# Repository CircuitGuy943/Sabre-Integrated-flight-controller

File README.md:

I am currently trying to build my own drone from scratch, and slowly replace every component with my own, from creating fully custom PCBs for the flight controller or ESCs, to making a 3D printed drone chassis etc etc. And this is the fully fledged, multi functional, cool-looking flight controller. I present to you:

# *SABRE!*

For one of my biggest projects yet I designed a jack of all trades custom flight controller board. It also comes with custom firmware, or if possible compatibility with betaflight or other FC firmware out there. At it's core are two PCBs arranged in a stackup with the "top" and "bottom" sections. The two PCBs connect through the common 2.54mm pitch headers and stack on top of eachother and each serve to provide enough space for all the components and separate the sensitive digital components from the electromagnetic potential of the motor power rails. The bottom board houses E-Fuse protection and an INA226 current monitor to protect the boards, including powered FPV feed with the AT7456E and TX5813, accompanied by four MOSFET powered 12V LED strip channels. The top booard houses a powerful STM32F765VGT CPU which will, *fingers crossed,* be more than enough to run automatic flight levelling software quickly enough to not crash. Followed by a micro SD card slot for storing flight telemetry, programmable DIP switched for easy settings, BNO08x 9-DOF sensor module, segment display and pushbuttons for easy configuration without needing to reupload code and a BMP580 barometic sensor. More than I (or you) will ever need to fly a 4 blade, 1KG piece of PETG plastic :)

### Bottom Board:

Half of the bottom PCB houses the power delivery circuitry. This includes a dedicated TPS259850 chip, or an E-Fuse, required protection option for a drone that operates at around 20A sustained and 40A current peaks. Thanks to it's extremely low RDS on, basically no power is wasted, and it trips the circuit in a matter of microseconds when too much current is detected, which makes it extremely useful for a drone full of sensitive circuitry, compared to a traditional wire fuse. Followed by that is an INA226 chip, this aims to precisely monitor the current consumption of the entire drone, helping to predict flight times and efficiently manage battery health, through the use of a shunt resistor sized to the expected current draw. The current planes are optimized to make proper use of the different outer and inner layer thicknesses and properly distribute current with minimal heat up.

The other part of the bottom PCB houses the RF circuitry for the FPV system LED drivers togethor with power regulators that power the 12V rail for the LED drivers and the 5V rail for the FPV system and other 5V chips. The 12V power regulator (TPS55289) and the 5V regulator (TPS63070) both use the safest and most reliable layouts possible and are positioned to spatially divide the high ~32A currents on the bottom power distribution circuitry from the rest of the bottom board, a slide switch also controls the power supply to the TX5813 module, as this consumes the most out of the other board circuitry, at about ~200mA, this should help to increase flight time by cutting wasted power when the FPV function isn't being used. CSD16340 MOSFETS also serve to drive 4 seperate 12V LED strip channels, these I plan to connect to LED strips and create cool illuminations off of my drone.

The RF circuitry benefits from an impedance accurate JLC-3313 stackup and use of coplanar waveguide routing with via fencing, tearsrops and udnerpad via router to insure the least impedance mismatch possible. The actual RF system is composed of an external camera connector, or simple pin header (capable of reading almost any FPV camera such as the Caddx Ant Lite). The video signal is then passed through a meticulously routed 75ohm impedance matched trace into a MAX7456EUI (Or a newer drop in AT7456E replacement, pin to pin compatible), this module serves to inject an OSD (On screen display) into the video feed through communication with the STM32 MCU for easy sending of telemtry data like battery voltage, speed, altitude etc. The output from the OSD injection chip is then routed through another impedance matched trace with SAG correction into the video input of the TX5813. This modules handles the complicated circuitry of converting the video feed (~6MHz) into a radio signal of ~5.8GHz. That RF is then routed even more carefuly for the short length (~8mm) of the SMA launch into the SMA connector then into any respective 5.8GHz FPV antenna. (I also have a complemintary project for a 5.8GHz FPV reciever in another repository)

### Top Board:

Flying the drone is an STM32F765VGT CPU with up to 216MHz clock speed, hopefully resulting in almost perfect drone levelling and flight, on the other side of the board is also a USB C receptacle for programming the STM CPU, and powering the board while doing so (everything except the motors, of course, I also included diodes to prevent power backfeed). Close by is a BNO08x 9-DOF accelerometer, gyroscope and magnetometer, complete with an integrated 32-bit ARM Cortex-M0+ for quick sensor fusion with pre built firmware (meaning I have to code waaaay less :D). Motor PWM outputs for the ESCs also connected directly to PWM channels on the STM32 and two solder bridgeable connections to allow me to use the 5V supply from the ESCs in case my 5V regulator doesn't function properly under load (I've had bad experience with voltage regulators). Several voltage indicator LEDs are also placed near the USB C port at the back. Then there is also an UART FPC port designed to connect to a separate GPS board (large board for good GPS recieving power, check my other repositories) on the left side of the board. A 7 segment, 4 digit bitbanged display and several tactile pushbottoms also occupy the centre of the board, quite useless but they might be useful in changing more accute settings without having to reupload firmware every time. A micro SD card also connects through 4 channel SPI to STM32, I plan to use this to store settings or flight telemetry information that I could analyze while debugging. Powering all that is a 3.3V regulator (LMR51430XF), simplest (and therefore most reliable) I could find. And several other breakout headers for power/functionality. PWM inputs from the radio remote is recieved through a 3x8 header pinout designed for my specific radio reciever module.

## Features:
- Fully integrated design:
	- Custom firmware uploadable
	- Power distribution and control in one place
	- Dual stacked PCB design
 	- No screw, no wire inter board connection

- Power
	- Extremely low RDS protection e-Fuse (us trip time)
 	- INA226 current and voltage monitoring
  	- Backup/calibration voltage divider monitoring
  	- Fully optimized current planes, 40A+ capability
  	- Firmware built in battery management and flight warning system
  	- Meticulously designed 5V, 12V and 3.3V switching voltage regulators
  	- Backup ESC 5V supply availible
  	- LED indicators for power rail status
  	- 4 channel driver for 12V LED strips
  	- Power switch for TX5813 module for longer flight times

- Fully integrated FPV support
	- MAX7456/AT7456E OSD injection into FPV feed
	- Channel switch ability
	- TX5813 RF launch module
	- Accurate and reliable RF design
 	- Designed for impedance matched JLC 3313 stackup
 
- Flight Control
	- USB C programming connection 
	- Powerful STM32F765VGT CPU
 	- MicroSD card slot (For inflight telemtry storage)
  	- Programmable DIP switches
  	- Display/pushbuttons for setting adjustment without code reupload
  	- BNO08x 9-DOF sensor module with built in sensor fusion
  	- BMP580 Barometric sensor
  	- UART FPC connection for external GPS board
  	- Extra power and I2C debug headers
  	- 7 input PWM channels
  	- 4 ESC output PWM channels

## PCB
This is the PCB, with L1 to L4 Layers, silkscreen for both layers and an all layers view

And here is the schematic

## Firmware Overview
I've included some basic firmware (**untested**) that should get the TFT display working out of the box with a quick upload from arduino IDE

## BOM:
The BOM list for the actual PCB components is in the BOM folder section and here is also a BOM list for all the other components I plan to buy for this:

- PCB             $378.08		
- Antenna         $7.77      https://www.aliexpress.com/item/1005006153683653.html		
- 90 degree SMA   $4.51      https://www.aliexpress.com/item/1005005665998117.html						
- TX5813 module   $15.82     https://www.aliexpress.com/item/1005011698073364.html
											
Total			      $406.18

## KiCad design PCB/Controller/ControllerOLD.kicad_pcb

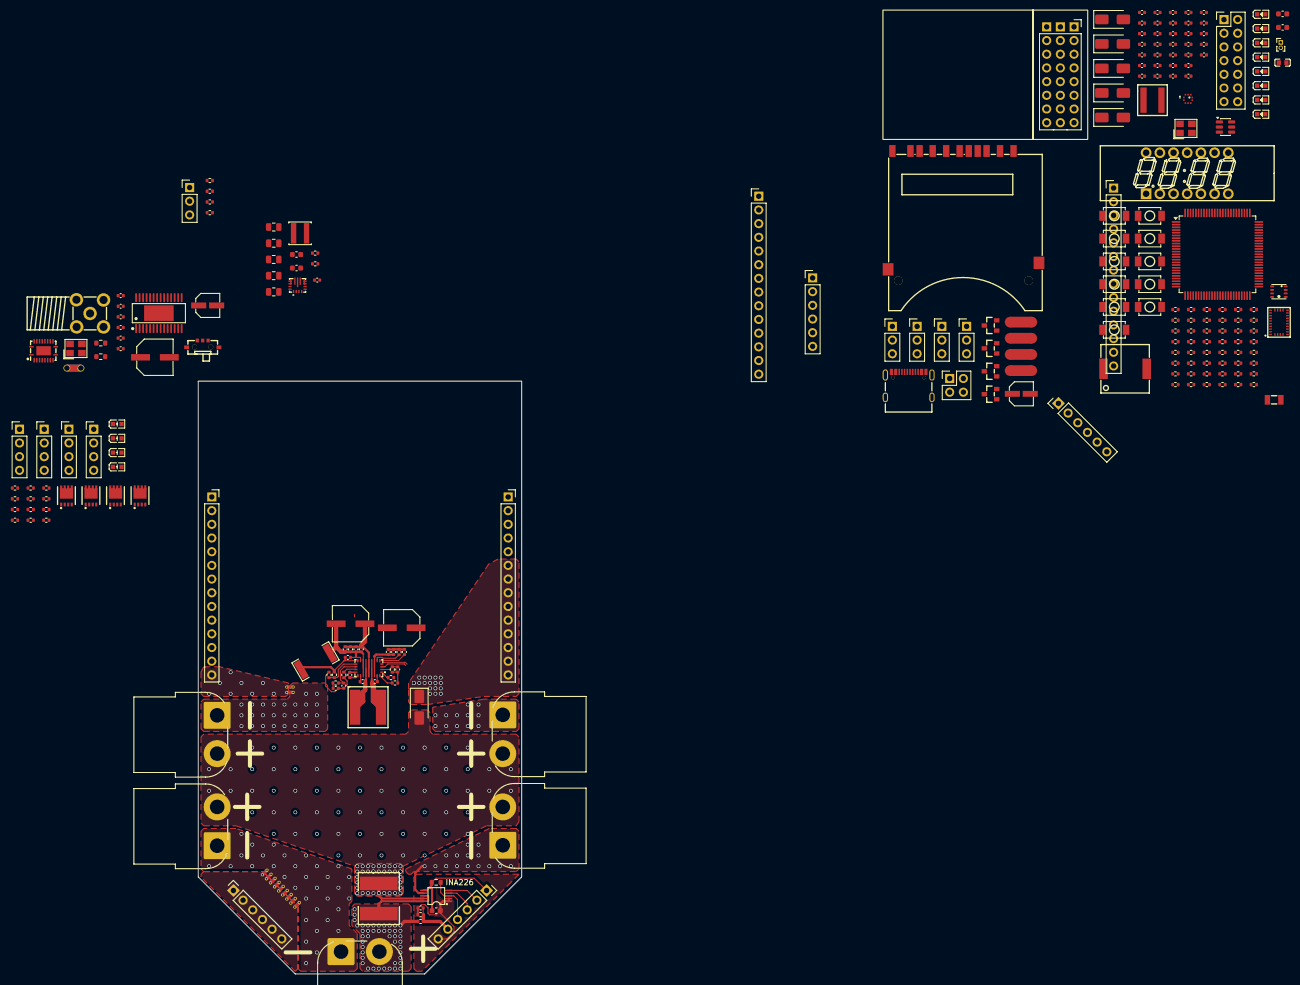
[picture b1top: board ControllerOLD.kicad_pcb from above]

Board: 4 copper layers, 60.0 x 110.0 mm, 254 parts (1 on the bottom side), 202 nets.

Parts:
BUZ1: CPT-9019S-SMT-TR; BUZ-SMD_L9.0-W9.0-P8.00-LS9.3
C1: 0.1uF; C_0603_1608Metric
C2, C11, C14, C15, C26, C27, C29, C30, C31, C32, C33, C34, C36, C37, C38, C41, C44, C45, C46, C47, C48, C49, C50, C51, C63, C64, C67: 100nF; C_0402_1005Metric
C3, C6: 10uF; C_0603_1608Metric
C4, C5: 10uF; C_0805_2012Metric
C7, C8, C9: 22uF; C_0805_2012Metric
C10, C57, C58: 2.2uF; C_0402_1005Metric
C12, C13: 22uF; C_0603_1608Metric
C16, C19, C20, C21, C22: 22uF; C_0402_1005Metric
C17: 4.7uF; C_0402_1005Metric
C18, C28: 22nF; C_0402_1005Metric
C23: 3300pF; C_0402_1005Metric
C24: 330pF; C_0402_1005Metric
C25: 47uF; CAP-SMD_BD6.3-L6.6-W6.6-LS7.2-FD
C35, C43, C56, C68: 10uF; C_0402_1005Metric
C39, C40, C60, C61: 20pF; C_0402_1005Metric
C42, C66: RVT1C220M0405_C3356_22uF; CAP-SMD_BD4.0-L4.3-W4.3-FD-LS5.3
C52, C53, C54, C55, C65: 1uF; C_0402_1005Metric
C59, C62: 6.8pF; C_0402_1005Metric
CN1: XT60PW_M; AMASS_XT60PW-M_1x02_P7.20mm_Horizontal
CN2, CN4, CN5, CN6: XT60PW_F; AMASS_XT60PW-F_1x02_P7.20mm_Horizontal
Card1: SD-006M; SD-SMD_SD-006M
D1, D2, D3, D4, D5, D6: SS34; D_SMA
J1, J2, J3, J4: Conn_01x04_Pin; PinHeader_1x04_P2.54mm_Vertical
J5, J6, J7, J8, J10: Conn_01x03_Pin; PinHeader_1x03_P2.54mm_Vertical
J9: Conn_01x02_Pin; PinHeader_1x02_P1.00mm_Vertical
J11: Conn_02x07_Top_Bottom; PinHeader_2x07_P2.54mm_Vertical
J12: Conn_02x02_Top_Bottom; PinHeader_2x02_P2.54mm_Vertical
J13, J18: Conn_01x14_Pin; PinHeader_1x14_P2.54mm_Vertical
J14, J19: Conn_01x06_Pin; PinHeader_1x06_P2.54mm_Vertical
J15, J20: Conn_01x14_Socket; PinSocket_1x14_P2.54mm_Vertical
J16, J17: Conn_01x06_Socket; PinSocket_1x06_P2.54mm_Vertical
L1: XFL4020-152MEC; IND-SMD_L4.0-W4.0-A
L2: FCM1608KF-601T03; L0603
LED1: FJ2481CH; LED-SEG-TH_14P-L32.2-W10.2-P2.54-S7.62-BL
LED2, LED11, LED12, LED13, LED14, LED15, LED16: KT-0603YG; LED0603-RD
LED3: KT-0603R; LED0603-RD
LED4, LED5, LED6, LED7: KT-0603W; LED0603-R-RD_WHITE
NT1, NT7, NT8, NT9, NT10, NT11, NT12, NT13, NT14, NT15, NT16: NetTie_2; NetTie-2_THT_Pad0.3mm
NT2: NetTie_2; NetTie-2_THT_Pad1.0mm
NT3, NT4, NT5, NT6: NetTie_2; NetTie-2_SMD_Pad2.0mm
Q1, Q2, Q3, Q5: CSD16340Q3; VSON-CLIP-8_L3.3-W3.3-P0.65-BL
Q7, Q8, Q9, Q10: LBSS138LT1G; SOT-23_L2.9-W1.3-P1.90-LS2.4-BR
R1, R2: 5.1K; R_0402_1005Metric
R3: HOLR2725D-4W-2MR-1%; R2725
R4, R17, R18, R19, R21, R36, R37, R38, R39, R40, R41, R42, R43, R44, R45, R46, R47, R48, R60, R67, R68, R69, R76, R77, R82: 220; R_0402_1005Metric
R5, R72, R73, R74, R75: 680; R_0402_1005Metric
R6, R7, R12, R20, R22, R27, R28, R29, R30, R31, R34, R35, R58, R59, R61, R62, R63, R64, R65, R66, R88, R96, R97, R98, R102: 10K; R_0402_1005Metric
R8, R9: 100K; R_0402_1005Metric
R10: 22.1K; R_0402_1005Metric
R11: 68K; R_0402_1005Metric
R13, R14: 56K; R_0402_1005Metric
R15: MS122WF100MT4E; R2512
R16, R99, R100, R103, R104: 4.7K; R_0402_1005Metric
R23: 150K; R_0402_1005Metric
R24: 47K; R_0402_1005Metric
R25, R26: 2.2K; R_0402_1005Metric
R78: 100; R_0402_1005Metric
R83, R84: 75; R_0603_1608Metric
R85, R86, R87: 1K; R_0402_1005Metric
R101: 10K; R_0603_1608Metric
SW1, SW2, SW3, SW4, SW5, SW6, SW7, SW8, SW9, SW11, SW12: TS-1088-AR02016; SW-SMD_L3.9-W3.0-P4.45
SW13: MK-11C04-G013; SW-SMD_MK-11C04-G013
U1: STM32F765VGTx; LQFP-100_14x14mm_P0.5mm
U2: BNO080; LGA-28_L5.2-W3.8-P0.50-BL-1
U3: BMP580; LGA-10_L2.0-W2.0-P0.50-TL_BMP580
U4: XAL5050-562MEC; IND-SMD_L5.5-W5.3
U5: MAX7456EUI; HTSSOP-28_L9.7-W4.4-P0.65-LS6.4-BL-EP5.5
U6: SMA_Conn; SMA-TH_SMA-KWE_C7498154
U7: TPS55289RYQR; VQFN-21_L5.0-W3.0-P0.50-TL
U8: XAL7070-472MEC; IND-SMD_L7.5-W7.2-1
U9: TPS630701RNMT; VQFN-15_L3.0-W2.5-P0.50-BL
U10: MC7RE
U11: INA226AQDGSRQ1; VSSOP-10_L3.0-W3.0-P0.50-LS4.9-BL
U12: LMR51430; SOT-23-6
U13, U18: 100uF; CAP-SMD_BD6.3-L6.6-W6.6-LS7.2-FD-1
U14: BME280; LGA-8_BME280_BL
U15: S322527M20PF10PPM; CRYSTAL-SMD_4P-L3.2-W2.5-BL
U16: TXB0108RGYR; VQFN-20_L4.5-W3.5-P0.50-BL-EP
U17: TX5813
USB1: TYPE-C 16P(073); USB-C-SMD_TYPE-C16PIN_C668624
X1: X322525MOB4SI; CRYSTAL-SMD_4P-L3.2-W2.5-BL
X2: Q13FC1350000400; FC-135R_L3.2-W1.5

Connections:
+3.3V: C12.2, C13.2, C29.1, C30.1, C32.2, C33.2, C34.2, C42.1, C43.1, C45.1, C46.1, C47.1, C48.1, C49.1, C50.1, C51.1, C52.1, C53.1, C54.1, C55.1, C56.1, C64.1, C65.1, C67.1, C68.1, Card1.4 (VDD), J11.12, J11.13, J14.1, J18.5, L2.2, LED16.2 (A), R6.2, R9.1, R25.2, R26.2, R27.1, R58.2, R59.2, R61.2, R62.2, R63.2, R64.2, R65.2, R66.2, R96.1, R97.1, R98.1, R99.1, R100.1, R102.1, R103.2, R104.2, SW1.2, SW2.2, SW3.2, SW4.2, SW5.2, SW6.2, SW7.2, SW8.2, SW9.2, SW12.1, U1.6 (VBAT), U1.11 (VDD), U1.20 (VREF+), U1.27 (VDD), U1.50 (VDD), U1.75 (VDD), U1.100 (VDD), U2.3 (VDD), U2.5 (PS1), U2.28 (VDDIO), U3.1 (VDDIO), U3.10 (VDD), U4.2, U14.2 (CSB), U14.6 (VDDIO), U14.8 (VDD)
+3.3V_B: C1.2, J16.1, J20.5, LED4.1 (A), LED5.1 (A), LED6.1 (A), LED7.1 (A), R28.1, R101.2, U11.6 (VS+), U16.2 (VCCA), U16.10 (OE)
+5V: J9.2, J11.10, J11.11, J18.4, LED15.2 (A), U10.17 (5V), U10.18 (5V), U10.19 (5V), U10.20 (5V), U10.21 (5V), U10.22 (5V), U10.23 (5V), U10.24 (SBUS3)
+5V_B: C6.2, C7.2, C8.2, C9.2, C17.2, J10.1, J20.4, R8.2, R85.2, R86.2, R87.2, R88.2, SW13.1, U7.18 (VCC), U9.5 (FB), U9.7 (VOUT), U16.19 (VCCB)
+12V: J11.8, J11.9, J18.3, LED14.2 (A)
+12V_B: C26.1, J2.1, J2.2, J2.3, J2.4, J3.1, J3.2, J3.3, J3.4, J20.3, R11.2, R15.2, U7.13 (ISN)
BMP580_INT: R102.2, U1.96 (PB9), U3.7 (INT)
BNO580_BOOTN: R27.2, U1.34 (PB0), U2.4 (BOOTN)
BNO580_CSN: U1.77 (PA15), U2.18 (H_CSN)
BNO580_INTN: R98.2, U1.33 (PC5), U2.14 (H_INTN)
BNO580_MISO: U1.30 (PA6), U2.20 (H_SDA/H_MISO/TX)
BNO580_MOSI: U1.31 (PA7), U2.17 (SA0/H_MOSI)
BNO580_NRST: R97.2, U1.32 (PC4), U2.11 (NRST)
BNO580_SCLK: U1.29 (PA5), U2.19 (H_SCL/SCK/RX)
BNO580_WAKE: R96.2, U1.35 (PB1), U2.6 (PS0/WAKE)
BOOT: R22.1, SW12.2, U1.94 (BOOT0)
BOOT1: C14.2, U7.8 (SW1), U8.2
BOOT2: C15.2, U7.10 (SW2), U8.1
BUTTON_DECREASE: SW4.1, U1.39 (PE9)
BUTTON_F1: SW6.1, U1.41 (PE11)
BUTTON_F2: SW7.1, U1.42 (PE12)
BUTTON_F3: SW8.1, U1.43 (PE13)
BUTTON_F4: SW9.1, U1.51 (PB12)
BUTTON_INCREASE: SW3.1, U1.38 (PE8)
BUTTON_LEFT: SW1.1, U1.36 (PB2)
BUTTON_OK: SW5.1, U1.40 (PE10)
BUTTON_RIGHT: SW2.1, U1.37 (PE7)
BUZZER: R78.1, U1.53 (PB14)
DISP_A: R41.2, U1.87 (PD6)
DISP_B: R44.2, U1.86 (PD5)
DISP_C: R38.2, U1.85 (PD4)
DISP_D: R39.2, U1.84 (PD3)
DISP_D2D1: R45.2, U1.58 (PD11)
DISP_DIG1: R46.1, U1.91 (PB5)
DISP_DIG2: R48.1, U1.90 (PB4)
DISP_DIG3: R36.1, U1.89 (PB3)
DISP_DIG4: R47.1, U1.88 (PD7)
DISP_DP: R40.2, U1.67 (PA8)
DISP_E: R37.2, U1.72 (PA13)
DISP_F: R42.2, U1.69 (PA10)
DISP_G: R43.2, U1.68 (PA9)
EXTRA_I2C_EN: J12.4, U1.44 (PE14)
EXTRA_I2C_INT: J12.3, U1.45 (PE15)
EXTRA_I2C_SCL: J12.1, R103.1, U1.46 (PB10)
EXTRA_I2C_SDA: J12.2, R104.1, U1.47 (PB11)
GND: BUZ1.2 (-), C10.2, C29.2, C30.2, C31.1, C32.1, C33.1, C34.1, C35.2, C42.2, C43.2, C45.2, C46.2, C47.2, C48.2, C49.2, C50.2, C51.2, C52.2, C53.2, C54.2, C55.2, C56.2, C57.1, C58.1, C59.2, C60.2, C61.1, C62.2, C63.2, C64.2, C65.2, C67.2, C68.2, Card1.3 (Vss1), Card1.6 (Vss2), Card1.12, Card1.13, J5.3, J6.3, J7.3, J8.3, J11.5, J11.6, J11.7, J11.14, J13.14, J14.6, J19.1, J19.2, J19.3, J19.4, J19.5, J19.6, NT3.1, NT4.1, NT5.1, NT6.1, Q7.2 (S), Q8.2 (S), Q9.2 (S), Q10.2 (S), R1.2, R2.2, R4.2, R5.2, R10.2, R22.2, R72.2, R73.2, R74.2, R75.2, R76.2, R77.2, R82.2, SW11.1, U1.10 (VSS), U1.19 (VSSA), U1.26 (VSS), U1.49 (VSS), U1.74 (VSS), U1.99 (VSS), U2.2 (GND), U2.25 (GND), U2.26 (XOUT32/CLKSEL1), U3.3 (VSS), U3.5 (SDO), U3.6 (CSB), U3.8 (VSS), U3.9 (VSS), U10.9 (GND), U10.10 (GND), U10.11 (GND), U10.12 (GND), U10.13 (GND), U10.14 (GND), U10.15 (GND), U10.16 (SBUS2), U12.1 (GND), U14.1 (GND), U14.7 (GND), USB1.1 (SHELL), USB1.2 (SHELL), USB1.3 (SHELL), USB1.4 (SHELL), USB1.A1B12 (GND), USB1.B1A12 (GND), X1.2 (GND), X1.4 (GND)
GND_B: C1.1, C2.2, C3.1, C4.1, C5.1, C6.1, C7.1, C8.1, C9.1, C16.1, C17.1, C18.1, C19.1, C20.1, C21.1, C22.1, C23.1, C24.1, C25.1, C27.1, C28.1, C36.1, C37.1, C38.1, C39.2, C40.1, C44.2, J10.2, J15.14, J16.6, J17.1, J17.2, J17.3, J17.4, J17.5, J17.6, NT1.1, NT2.2, NT7.1, NT8.1, NT9.1, NT10.1, NT11.1, NT12.1, NT13.1, NT14.1, NT15.1, NT16.1, Q1.1 (S), Q1.2 (S), Q1.3 (S), Q2.1 (S), Q2.2 (S), Q2.3 (S), Q3.1 (S), Q3.2 (S), Q3.3 (S), Q5.1 (S), Q5.2 (S), Q5.3 (S), R13.1, R14.2, R16.1, R20.2, R24.2, R29.1, R30.1, R31.1, R34.1, R35.1, R83.2, SW13.4, SW13.5, U5.4 (DGND), U5.20 (AGND), U5.23 (PGND), U5.29 (EP), U7.9 (PGND), U7.17 (AGND), U9.4 (GND), U9.6 (FB2), U9.10 (PGND), U9.15 (VSEL), U11.1 (A1), U11.2 (A0), U13.1, U15.2 (GND), U15.4 (GND), U16.11 (GND), U16.21 (EP)
HSE_IN: C61.2, U1.12 (PH0), X1.1 (OSC1)
HSE_OUT: C60.1, U1.13 (PH1), X1.3 (OSC2)
INA_ALERT: LED3.2 (A), R6.1
INA_ALERT_B: J16.4, R101.1, U11.3 (Alert)
INA_ALERT_T: J14.4, U1.95 (PB8)
LED1_POWER: J1.1, J4.1, Q1.5 (D), Q1.6 (D), Q1.7 (D), Q1.8 (D), R67.2
LED1_PWM_B: J15.1, R17.2
LED1_PWM_T: J13.1, U1.15 (PC0)
LED2_POWER: J1.2, J4.2, Q2.5 (D), Q2.6 (D), Q2.7 (D), Q2.8 (D), R60.2
LED2_PWM_B: J15.2, R18.2
LED2_PWM_T: J13.2, U1.16 (PC1)
LED3_POWER: J1.3, J4.3, Q5.5 (D), Q5.6 (D), Q5.7 (D), Q5.8 (D), R68.2
LED3_PWM_B: J15.3, R21.2
LED3_PWM_T: J13.3, U1.17 (PC2)
LED4_POWER: J1.4, J4.4, Q3.5 (D), Q3.6 (D), Q3.7 (D), Q3.8 (D), R69.2
LED4_PWM_B: J15.4, R19.2
LED4_PWM_T: J13.4, U1.18 (PC3)
LSE_IN: C59.1, U1.8 (PC14), X2.1
LSE_OUT: C62.1, U1.9 (PC15), X2.2
MAIN_SCK_B: J15.6, J16.2, U7.3 (SCL), U11.5 (SCL)
MAIN_SCK_T: J13.6, J14.2, R99.2, U1.92 (PB6)
MAIN_SDA_B: J15.7, J16.3, U7.4 (SDA), U11.4 (SDA)
MAIN_SDA_T: J13.7, J14.3, R100.2, U1.93 (PB7)
MAX7456_CS_3.3V_B: J15.11, U16.6 (A5)
MAX7456_CS_3.3V_T: J13.11, U1.3 (PE4)
MAX7456_CS_5V: U5.8 (~CS), U16.15 (B5)
MAX7456_HSYNC_5V: R87.1, U5.18 (~HSYNC)
MAX7456_LOS_3.3V_B: J15.12, U16.4 (A3)
MAX7456_LOS_3.3V_T: J13.12, U1.2 (PE3)
MAX7456_LOS_5V: R86.1, U5.12 (LOS), U16.17 (B3)
MAX7456_RESET_3.3V_B: J15.13, U16.3 (A2)
MAX7456_RESET_3.3V_T: J13.13, U1.98 (PE1)
MAX7456_RESET_5V: R88.1, U5.19 (~RESET), U16.18 (B2)
MAX7456_SCLK_3.3V_B: J15.8, U16.9 (A8)
MAX7456_SCLK_3.3V_T: J13.8, U1.1 (PE2)
MAX7456_SCLK_5V: U5.10 (SCLK), U16.12 (B8)
MAX7456_SDIN_3.3V_B: J15.9, U16.8 (A7)
MAX7456_SDIN_3.3V_T: J13.9, U1.5 (PE6)
MAX7456_SDIN_5V: U5.9 (SDIN), U16.13 (B7)
MAX7456_SDOUT_3.3V_B: J15.10, U16.7 (A6)
MAX7456_SDOUT_3.3V_T: J13.10, U1.4 (PE5)
MAX7456_SDOUT_5V: U5.11 (SDOUT), U16.14 (B6)
MAX7456_VSYNC_5V: R85.1, U5.17 (~VSYNC)
MGND_B: CN1.1 (-), CN2.2, CN4.2, CN5.2, CN6.2, NT1.2, NT7.2, NT8.2, NT9.2, NT10.2, NT11.2, NT12.2, NT13.2, NT14.2, NT15.2, NT16.2, U11.7 (GND)
MOTOR_PWM1: J5.1, U1.22 (PA0)
MOTOR_PWM2: J6.1, U1.23 (PA1)
MOTOR_PWM3: J7.1, U1.24 (PA2)
MOTOR_PWM4: J8.1, U1.25 (PA3)
unnamed: BUZ1.1 (+), R78.2
unnamed: C24.2, R12.1
unnamed: C66.2, R84.2, U18.1
unnamed: D3.2 (A), J5.2
unnamed: D3.1 (K), D4.1 (K), D5.1 (K), D6.1 (K), J9.1
unnamed: D4.2 (A), J6.2
unnamed: D5.2 (A), J7.2
unnamed: D6.2 (A), J8.2
unnamed: LED1.14 (A), R42.1
unnamed: LED1.8 (B), R44.1
unnamed: LED1.6 (C), R38.1
unnamed: LED1.11 (D2D1), R41.1
unnamed: LED1.2 (D), LED1.7 (D), R39.1
unnamed: LED1.1 (DIG1), Q7.3 (D)
unnamed: LED1.12 (DIG2), Q10.3 (D)
unnamed: LED1.5 (DIG3), Q8.3 (D)
unnamed: LED1.9 (DIG4), Q9.3 (D)
unnamed: LED1.3 (DP), R40.1
unnamed: LED1.4 (E), R37.1
unnamed: LED1.13 (F), R45.1
unnamed: LED1.10 (G), R43.1
unnamed: LED2.1 (K), R72.1
unnamed: LED3.1 (K), R4.1
unnamed: LED4.2 (K), R67.1
unnamed: LED5.2 (K), R60.1
unnamed: LED6.2 (K), R68.1
unnamed: LED7.2 (K), R69.1
unnamed: LED11.1 (K), R5.1
unnamed: LED12.1 (K), R73.1
unnamed: LED13.1 (K), R74.1
unnamed: LED14.1 (K), R75.1
unnamed: LED15.1 (K), R76.1
unnamed: LED16.1 (K), R77.1, R82.1
unnamed: NT2.1, U6.3, U6.4, U17.3 (AGND)
unnamed: Q1.4 (G), R17.1, R29.2
unnamed: Q2.4 (G), R18.1, R30.2
unnamed: Q3.4 (G), R19.1, R34.2
unnamed: Q5.4 (G), R21.1, R31.2
unnamed: Q7.1 (G), R46.2
unnamed: Q8.1 (G), R36.2
unnamed: Q9.1 (G), R47.2
unnamed: Q10.1 (G), R48.2
unnamed: C57.2, U1.48 (VCAP_1)
unnamed: C58.2, U1.73 (VCAP_2)
unnamed: L2.1, U1.21 (VDDA)
unnamed: C31.2, U2.9 (CAP), U2.10 (CLKSEL0)
unnamed: C66.1, U5.25 (SAG)
unnamed: C41.2, U5.22 (VIN)
unnamed: U5.26 (VOUT), U18.2
unnamed: C14.1, U7.20 (BOOT1)
unnamed: C15.1, U7.19 (BOOT2)
unnamed: R13.2, U7.16 (CDC)
unnamed: C23.2, R12.2, U7.15 (COMP)
unnamed: C18.2, U7.5 (DITH/SYNC)
unnamed: R20.1, U7.21 (EXTVCC)
unnamed: R11.1, R16.2, U7.14 (FB/~INT)
unnamed: R14.1, U7.6 (FSW)
unnamed: C19.2, C20.2, C21.2, C22.2, C25.2, C26.2, R15.1, U7.11 (VOUT), U7.12 (ISP)
unnamed: C44.1, R35.2, U7.2 (MODE)
unnamed: R7.2, U9.1 (PS/S), U9.14 (EN)
unnamed: L1.1, U9.11 (L1)
unnamed: L1.2, U9.9 (L2)
unnamed: R8.1, U9.2 (PG)
unnamed: C2.1, U9.3 (VAUX)
unnamed: C11.1, U12.6 (CB)
unnamed: C12.1, C13.1, R9.2, R10.1, U12.4 (FB)
unnamed: C11.2, U4.1, U12.2 (SW)
unnamed: R26.1, U2.15 (ENV_SCL), U14.4 (SCK)
unnamed: R25.1, U2.16 (ENV_SDA), U14.3 (SDI)
unnamed: U6.1, U6.2, U17.1 (AGND)
unnamed: U6.5, U17.2 (ANT)
unnamed: R2.1, USB1.A5 (CC1)
unnamed: R1.1, USB1.B5 (CC2)
PGND: NT3.2, NT4.2, NT5.2, NT6.2
RADIO_PWM1: U1.59 (PD12), U10.1 (CH1)
RADIO_PWM2: U1.60 (PD13), U10.2 (CH2)
RADIO_PWM3: U1.61 (PD14), U10.3 (CH3)
RADIO_PWM4: U1.62 (PD15), U10.4 (CH4)
RADIO_PWM5: U1.63 (PC6), U10.5 (CH5)
RADIO_PWM6: U1.64 (PC7), U10.6 (CH6)
RESET: C63.1, SW11.2, U1.14 (NRST)
SD_CD: Card1.CD, R58.1, U1.82 (PD1)
SD_CLK: Card1.5 (CLK), R64.1, U1.80 (PC12)
SD_CMD: Card1.2 (CMD), R65.1, U1.83 (PD2)
SD_DAT0: Card1.7 (DAT0), R63.1, U1.65 (PC8)
SD_DAT1: Card1.8 (DAT1), R62.1, U1.66 (PC9)
SD_DAT2: Card1.9 (DAT2), R61.1, U1.78 (PC10)
SD_DAT3: Card1.1 (CD/DAT3), R66.1, U1.79 (PC11)
SD_WP: Card1.WP, R59.1, U1.81 (PD0)
TPS_ENABLE_B: J15.5, R28.2, U7.1 (EN/UVLO)
TPS_ENABLE_T: J13.5, U1.97 (PE0)
USB_DN: U1.70 (PA11), USB1.A7 (DN1), USB1.B7 (DN2)
USB_DP: U1.71 (PA12), USB1.A6 (DP1), USB1.B6 (DP2)
VBAT: J11.1, J18.1, LED11.2 (A)
VBAT_B: CN1.2 (+), J20.1, R3.2, R23.1, U11.8 (VBUS), U11.10 (VIN+)
VBUS: C35.1, D1.2 (A), J11.2, LED2.2 (A), USB1.A4B9 (VBUS), USB1.B4A9 (VBUS)
VIDEO: J10.3, R84.1
VIDEO_OSD: C41.1, R83.1
VMOTORS: J11.3, J18.2, LED12.2 (A)
VMOTORS_B: CN2.1, CN4.1, CN5.1, CN6.1, D2.2 (A), J20.2, R3.1, U11.9 (VIN-)
VOLTAGE_ADC_B: C28.2, J16.5, R23.2, R24.1
VOLTAGE_ADC_T: J14.5, U1.28 (PA4)
VSYS: C10.1, D1.1 (K), J11.4, J18.6, J18.7, J18.8, J18.9, J18.10, J18.11, J18.12, J18.13, J18.14, LED13.2 (A), U12.3 (VIN), U12.5 (EN)
VSYS_B: C3.2, C4.2, C5.2, C16.2, C27.2, D2.1 (K), J20.6, J20.7, J20.8, J20.9, J20.10, J20.11, J20.12, J20.13, J20.14, R7.1, U7.7 (VIN), U9.12 (VIN), U13.2
VTX_SUPPLY: C36.2, C37.2, C38.2, SW13.C, U5.3 (DVDD), U5.21 (AVDD), U5.24 (PVDD)
XTAL1: C40.2, U5.5 (CLKIN), U15.3
XTAL2: C39.1, U5.6 (XFB), U15.1

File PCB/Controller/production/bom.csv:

Designator,Footprint,Quantity,Value,LCSC Part #
BUZ1,BUZ-SMD_L9.0-W9.0-P8.00-LS9.3,1,CPT-9019S-SMT-TR,C95163
C1,0603,1,0.1uF,
"C10, C57, C58",0402,3,2.2uF,
"C11, C14, C15, C2, C26, C27, C29, C30, C31, C32, C33, C34, C36, C37, C38, C41, C44, C45, C46, C47, C48, C49, C50, C51, C63, C64, C67, C78",0402,28,100nF,
"C12, C13",0603,2,22uF,
"C16, C19, C20, C21, C22",0402,5,22uF,
C17,0402,1,4.7uF,
"C18, C28",0402,2,22nF,
C23,0402,1,3300pF,
C24,0402,1,330pF,
C25,CAP-SMD_BD6.3-L6.6-W6.6-LS7.2-FD,1,47uF,C970677
"C3, C6",0603,2,10uF,
"C35, C43, C56, C68, C77",0402,5,10uF,
"C39, C40, C60, C61",0402,4,20pF,
"C4, C5",0805,2,10uF,
"C42, C66, C74",CAP-SMD_BD4.0-L4.3-W4.3-FD-LS5.3,3,RVT1C220M0405_C3356_22uF,C3356
"C52, C53, C54, C55, C65",0402,5,1uF,
"C59, C62",0402,2,6.8pF,
"C69, C75, C76",0402,3,0.1uF,
"C7, C8, C9",0805,3,22uF,
C70,0402,1,15nF,
C71,0402,1,3.3nF,
C72,0402,1,10nF,
C73,0402,1,150pF,
CARD2,TF-SMD_TF-01A,1,TF-01A,C91145
CN1,AMASS_XT60PW-M_1x02_P7.20mm_Horizontal,1,XT60PW_M,C98732
"CN2, CN4, CN5, CN6",AMASS_XT60PW-F_1x02_P7.20mm_Horizontal,4,XT60PW_F,C428722
"D1, D2, D3, D4, D5, D6",D_SMA,6,SS34,
J1,PinHeader_2x07_P2.54mm_Vertical,1,Conn_02x07_Odd_Even,
"J10, J5, J6, J7, J8",PinHeader_1x03_P2.54mm_Vertical,5,Conn_01x03_Pin,
J12,PinHeader_2x02_P2.54mm_Vertical,1,Conn_02x02_Top_Bottom,
"J13, J18",PinHeader_1x14_P2.54mm_Vertical,2,Conn_01x14_Pin,
"J14, J19",PinHeader_1x06_P2.54mm_Vertical,2,Conn_01x06_Pin,
"J15, J20",PinSocket_1x14_P2.54mm_Vertical,2,Conn_01x14_Socket,
"J16, J17",PinSocket_1x06_P2.54mm_Vertical,2,Conn_01x06_Socket,
"J2, J9",PinHeader_1x02_P1.00mm_Vertical,2,Conn_01x02_Pin,
J21,PinHeader_2x04_P2.54mm_Vertical,1,Conn_02x04_Odd_Even,
L1,IND-SMD_L4.0-W4.0-A,1,XFL4020-152MEC,C3033018
L2,L0603,1,FCM1608KF-601T03,C141723
LED1,LED-SEG-TH_14P-L32.2-W10.2-P2.54-S7.62-BL,1,FJ2481CH,C10707
"LED11, LED12, LED13, LED14, LED15, LED16, LED2, LED9",LED0603-RD,8,KT-0603YG,C2289
"LED3, LED8",LED0603-RD,2,KT-0603R,C2286
"LED4, LED5, LED6, LED7",LED0603-R-RD_WHITE,4,KT-0603W,C2290
"Q1, Q2, Q3, Q5",VSON-CLIP-8_L3.3-W3.3-P0.65-BL,4,CSD16340Q3,C47616
"Q10, Q7, Q8, Q9",SOT-23_L2.9-W1.3-P1.90-LS2.4-BR,4,LBSS138LT1G,C8490
"R1, R2",0402,2,5.1K,
R10,0402,1,22.1K,
"R100, R103, R104, R16, R99",0402,5,4.7K,
R101,0603,1,10K,
"R102, R12, R20, R22, R27, R28, R29, R30, R31, R34, R35, R49, R58, R6, R61, R62, R63, R64, R65, R66, R7, R88, R96, R97, R98",0402,25,10K,
"R11, R33",0402,2,68K,
"R13, R14",0402,2,56K,
R15,R2512,1,MS122WF100MT4E,C68609
"R17, R18, R19, R21, R36, R37, R38, R39, R4, R40, R41, R42, R43, R44, R45, R46, R47, R48, R60, R67, R68, R69, R76, R77, R82",0402,25,220,
R23,0402,1,150K,
R24,0402,1,47K,
"R25, R26, R55",0402,3,2.2K,
R3,R2725,1,HOLR2725D-4W-2MR-1%,C500746
"R32, R54, R85, R86, R87",0402,5,1K,
"R5, R72, R73, R74, R75",0402,5,680,
R50,0402,1,160,
R51,0402,1,1.1K,
R52,0402,1,48K,
R53,0402,1,1.5K,
R56,0402,1,50K,
R78,0402,1,100,
"R8, R9",0402,2,100K,
"R83, R84",0603,2,75,
"SW1, SW11, SW12, SW2, SW3, SW4, SW5, SW6, SW7, SW8, SW9",SW-SMD_L3.9-W3.0-P4.45,11,TS-1088-AR02016,C720477
"SW10, SW14",SW-SMD_DSIC03LSGET,2,DSIC03LSGET,C57453
SW13,SW-SMD_MK-11C04-G013,1,MK-11C04-G013,C778185
U1,LQFP-100_14x14mm_P0.5mm,1,STM32F765VGTx,
U10,MC7RE,1,~,
U11,VSSOP-10_L3.0-W3.0-P0.50-LS4.9-BL,1,INA226AQDGSRQ1,C2653835
U12,SOT-23-6,1,LMR51430XF,
"U13, U18",CAP-SMD_BD6.3-L6.6-W6.6-LS7.2-FD-1,2,100uF,C970685
U14,LGA-8_BME280_BL,1,BME280,C92489
U15,CRYSTAL-SMD_4P-L3.2-W2.5-BL,1,S322527M20PF10PPM,C7420779
U16,VQFN-20_L4.5-W3.5-P0.50-BL-EP,1,TXB0108RGYR,C194701
U17,TX5813,1,TX5813,
U19,QFN-26_L5.0-W4.5_TPS259850RQPR,1,TPS259850RQPR,C6290347
U2,LGA-28_L5.2-W3.8-P0.50-BL-1,1,BNO080,C717991
U20,SO-8_L4.9-W3.9-P1.27-LS6.0-BL,1,LD1117D33TR,C2971297
U3,LGA-10_L2.0-W2.0-P0.50-TL_BMP580,1,BMP580,C22391138
U4,IND-SMD_L5.5-W5.3,1,XAL5050-562MEC,C7305309
U5,HTSSOP-28_L9.7-W4.4-P0.65-LS6.4-BL-EP5.5,1,MAX7456EUI,C5346361
U6,SMA-TH_SMA-KWE_C7498154,1,SMA_Conn,C7498154
U7,VQFN-21_L5.0-W3.0-P0.50-TL,1,TPS55289RYQR,C5942077
U8,IND-SMD_L7.5-W7.2-1,1,XAL7070-472MEC,C3911513
U9,VQFN-15_L3.0-W2.5-P0.50-BL,1,TPS630701RNMT,C181473
USB1,USB-C-SMD_TYPE-C16PIN_C668624,1,TYPE-C 16P(073),C668624
X1,CRYSTAL-SMD_4P-L3.2-W2.5-BL,1,X322525MOB4SI,C9006
X2,FC-135R_L3.2-W1.5,1,Q13FC1350000400,C32346

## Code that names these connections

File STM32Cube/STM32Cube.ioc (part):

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Mcu.Name=STM32F765V(G-I)Tx
Mcu.Package=LQFP100
Mcu.UserName=STM32F765VGTx
PA0/WKUP.GPIOParameters=GPIO_ModeDefaultPP,GPIO_Speed,GPIO_Label
PA0/WKUP.GPIO_Label=MOTOR1
PA0/WKUP.GPIO_ModeDefaultPP=GPIO_MODE_AF_PP
PA0/WKUP.GPIO_Speed=GPIO_SPEED_FREQ_VERY_HIGH
PA0/WKUP.Signal=S_TIM2_CH1_ETR
PA1.GPIOParameters=GPIO_Speed,GPIO_Label
PA1.GPIO_Label=MOTOR2
PA1.GPIO_Speed=GPIO_SPEED_FREQ_VERY_HIGH
PA1.Signal=S_TIM2_CH2
PA10.GPIOParameters=GPIO_Label
PA10.GPIO_Label=DISP_F
PA10.Signal=GPIO_Output
PA11.Mode=Host_Only
PA11.Signal=USB_OTG_FS_DM
PA12.Mode=Host_Only
PA12.Signal=USB_OTG_FS_DP
PA13.GPIOParameters=GPIO_Label
PA13.GPIO_Label=DISP_E
PA13.Signal=GPIO_Output
PA15.GPIOParameters=GPIO_Label
PA15.GPIO_Label=BNO_NSS
PA15.Mode=NSS_Signal_Hard_Output
PA15.Signal=SPI1_NSS
PA2.GPIOParameters=GPIO_Speed,GPIO_Label
PA2.GPIO_Label=MOTOR3
PA2.GPIO_Speed=GPIO_SPEED_FREQ_VERY_HIGH
PA2.Signal=S_TIM2_CH3
PA3.GPIOParameters=GPIO_Speed,GPIO_Label
PA3.GPIO_Label=MOTOR3
PA3.GPIO_Speed=GPIO_SPEED_FREQ_VERY_HIGH
PA3.Signal=S_TIM2_CH4
PA4.GPIOParameters=GPIO_Label,GPIO_Mode
PA4.GPIO_Label=VOLTAGE_DIVIDER
PA4.GPIO_Mode=GPIO_MODE_ANALOG
PA4.Signal=ADCx_IN4
PA5.GPIOParameters=GPIO_Label
PA5.GPIO_Label=BNO_SCK
PA5.Mode=Full_Duplex_Master
PA5.Signal=SPI1_SCK
PA6.GPIOParameters=GPIO_Label
PA6.GPIO_Label=BNO_MISO
PA6.Mode=Full_Duplex_Master
PA6.Signal=SPI1_MISO
PA7.GPIOParameters=GPIO_Label
PA7.GPIO_Label=BNO_MOSI
PA7.Mode=Full_Duplex_Master
PA7.Signal=SPI1_MOSI
PA8.GPIOParameters=GPIO_Label
PA8.GPIO_Label=DISP_DP
PA8.Signal=GPIO_Output
PA9.GPIOParameters=GPIO_Label
PA9.GPIO_Label=DISP_G
PA9.Signal=GPIO_Output
PB0.GPIOParameters=PinState,GPIO_PuPd,GPIO_Label,GPIO_ModeDefaultOutputPP
PB0.GPIO_Label=BNO_BOOTN
PB0.GPIO_ModeDefaultOutputPP=GPIO_MODE_OUTPUT_PP
PB0.GPIO_PuPd=GPIO_PULLUP
PB0.PinState=GPIO_PIN_SET
PB0.Signal=GPIO_Output
PB1.GPIOParameters=PinState,GPIO_PuPd,GPIO_Label,GPIO_ModeDefaultOutputPP
PB1.GPIO_Label=BNO_WAKE
PB1.GPIO_ModeDefaultOutputPP=GPIO_MODE_OUTPUT_PP
PB1.GPIO_PuPd=GPIO_PULLUP
PB1.PinState=GPIO_PIN_SET
PB1.Signal=GPIO_Output
PB10.GPIOParameters=GPIO_Label
PB10.GPIO_Label=EXTRA_I2C_SCL
PB10.Mode=I2C
PB10.Signal=I2C2_SCL
PB11.GPIOParameters=GPIO_Label
PB11.GPIO_Label=EXTRA_I2C_SDA
PB11.Mode=I2C
PB11.Signal=I2C2_SDA
PB12.GPIOParameters=GPIO_Label
PB12.GPIO_Label=BUTTON_F4
PB12.Signal=GPIO_Input
PB13.GPIOParameters=GPIO_PuPd,GPIO_Label
PB13.GPIO_Label=DIP_CH1
PB13.GPIO_PuPd=GPIO_PULLDOWN
PB13.Signal=GPIO_Input
PB14.GPIOParameters=GPIO_Speed,GPIO_Label
PB14.GPIO_Label=BUZZER_PWM
PB14.GPIO_Speed=GPIO_SPEED_FREQ_VERY_HIGH
PB14.Signal=S_TIM12_CH1
PB15.GPIOParameters=GPIO_PuPd,GPIO_Label
PB15.GPIO_Label=DIP_CH2
PB15.GPIO_PuPd=GPIO_PULLDOWN
PB15.Signal=GPIO_Input
PB2.GPIOParameters=GPIO_Label
PB2.GPIO_Label=BUTTON_LEFT
PB2.Signal=GPIO_Input
PB3.GPIOParameters=GPIO_Label
PB3.GPIO_Label=DISP_DIG3
PB3.Signal=GPIO_Output
PB4.GPIOParameters=GPIO_Label
PB4.GPIO_Label=DISP_DIG2
PB4.Signal=GPIO_Output
PB5.GPIOParameters=GPIO_Label
PB5.GPIO_Label=DISP_DIG1
PB5.Signal=GPIO_Output
PB6.GPIOParameters=GPIO_Label
PB6.GPIO_Label=MAIN_I2C_SCL
PB6.Mode=I2C
PB6.Signal=I2C1_SCL
PB7.GPIOParameters=GPIO_Label
PB7.GPIO_Label=MAIN_I2C_SDA
PB7.Mode=I2C
PB7.Signal=I2C1_SDA
PB8.GPIOParameters=GPIO_PuPd,GPIO_Label,GPIO_ModeDefaultEXTI
PB8.GPIO_Label=INA_ALERT
PB8.GPIO_ModeDefaultEXTI=GPIO_MODE_IT_FALLING
PB8.GPIO_PuPd=GPIO_PULLUP
PB8.Signal=GPXTI8
PB9.GPIOParameters=GPIO_PuPd,GPIO_Label,GPIO_ModeDefaultEXTI
PB9.GPIO_Label=BMP_INT
PB9.GPIO_ModeDefaultEXTI=GPIO_MODE_IT_FALLING
PB9.GPIO_PuPd=GPIO_PULLUP
PB9.Signal=GPXTI9
PC0.GPIOParameters=GPIO_Speed,PinState,GPIO_PuPd,GPIO_Label,GPIO_ModeDefaultOutputPP
PC0.GPIO_Label=LEDSTRIP_PWM_1
PC0.GPIO_ModeDefaultOutputPP=GPIO_MODE_OUTPUT_PP
PC0.GPIO_PuPd=GPIO_PULLDOWN
PC0.GPIO_Speed=GPIO_SPEED_FREQ_VERY_HIGH
PC0.PinState=GPIO_PIN_RESET
PC0.Signal=GPIO_Output
PC1.GPIOParameters=GPIO_Speed,PinState,GPIO_PuPd,GPIO_Label,GPIO_ModeDefaultOutputPP
PC1.GPIO_Label=LEDSTRIP_PWM_2
PC1.GPIO_ModeDefaultOutputPP=GPIO_MODE_OUTPUT_PP
PC1.GPIO_PuPd=GPIO_PULLDOWN
PC1.GPIO_Speed=GPIO_SPEED_FREQ_VERY_HIGH
PC1.PinState=GPIO_PIN_RESET
PC1.Signal=GPIO_Output
PC10.Mode=SD_4_bits_Wide_bus
PC10.Signal=SDMMC1_D2
PC11.Mode=SD_4_bits_Wide_bus
PC11.Signal=SDMMC1_D3
PC12.Mode=SD_4_bits_Wide_bus
PC12.Signal=SDMMC1_CK
PC14/OSC32_IN.Mode=LSE-External-Oscillator
PC14/OSC32_IN.Signal=RCC_OSC32_IN
PC15/OSC32_OUT.Mode=LSE-External-Oscillator
PC15/OSC32_OUT.Signal=RCC_OSC32_OUT
PC2.GPIOParameters=GPIO_Speed,PinState,GPIO_PuPd,GPIO_Label,GPIO_ModeDefaultOutputPP
PC2.GPIO_Label=LEDSTRIP_PWM_3
PC2.GPIO_ModeDefaultOutputPP=GPIO_MODE_OUTPUT_PP
PC2.GPIO_PuPd=GPIO_PULLDOWN
PC2.GPIO_Speed=GPIO_SPEED_FREQ_VERY_HIGH
PC2.PinState=GPIO_PIN_RESET
PC2.Signal=GPIO_Output
PC3.GPIOParameters=GPIO_Speed,PinState,GPIO_PuPd,GPIO_Label,GPIO_ModeDefaultOutputPP
PC3.GPIO_Label=LEDSTRIP_PWM_4
PC3.GPIO_ModeDefaultOutputPP=GPIO_MODE_OUTPUT_PP
PC3.GPIO_PuPd=GPIO_PULLDOWN
PC3.GPIO_Speed=GPIO_SPEED_FREQ_VERY_HIGH
PC3.PinState=GPIO_PIN_RESET
PC3.Signal=GPIO_Output
PC4.GPIOParameters=GPIO_Speed,PinState,GPIO_PuPd,GPIO_Label
PC4.GPIO_Label=BNO_NRST
PC4.GPIO_PuPd=GPIO_PULLUP
PC4.GPIO_Speed=GPIO_SPEED_FREQ_LOW
PC4.PinState=GPIO_PIN_SET
PC4.Signal=GPIO_Output
PC5.GPIOParameters=GPIO_PuPd,GPIO_Label,GPIO_ModeDefaultEXTI
PC5.GPIO_Label=BNO_INTN
PC5.GPIO_ModeDefaultEXTI=GPIO_MODE_IT_FALLING
PC5.GPIO_PuPd=GPIO_PULLUP
PC5.Signal=GPXTI5
PC6.GPIOParameters=GPIO_Speed,GPIO_Label
PC6.GPIO_Label=RADIO_C2
PC6.GPIO_Speed=GPIO_SPEED_FREQ_VERY_HIGH
PC6.Signal=S_TIM3_CH1
PC7.GPIOParameters=GPIO_Speed,GPIO_Label
PC7.GPIO_Label=RADIO_C1
PC7.GPIO_Speed=GPIO_SPEED_FREQ_VERY_HIGH
PC7.Signal=S_TIM3_CH2
PC8.Mode=SD_4_bits_Wide_bus
PC8.Signal=SDMMC1_D0
PC9.Mode=SD_4_bits_Wide_bus
PC9.Signal=SDMMC1_D1
PD1.GPIOParameters=GPIO_PuPd,GPIO_Label
PD1.GPIO_Label=SD_CD
PD1.GPIO_PuPd=GPIO_PULLUP
PD1.Signal=GPIO_Input
PD10.GPIOParameters=GPIO_PuPd,GPIO_Label
PD10.GPIO_Label=DIP_CH3
PD10.GPIO_PuPd=GPIO_PULLDOWN
PD10.Signal=GPIO_Input
PD11.GPIOParameters=GPIO_Label
PD11.GPIO_Label=DISP_D2D1
PD11.Signal=GPIO_Output
PD12.GPIOParameters=GPIO_Speed,GPIO_Label
PD12.GPIO_Label=RADIO_C6
PD12.GPIO_Speed=GPIO_SPEED_FREQ_VERY_HIGH
PD12.Signal=S_TIM4_CH1
PD13.GPIOParameters=GPIO_Speed,GPIO_Label
PD13.GPIO_Label=RADIO_C5
PD13.GPIO_Speed=GPIO_SPEED_FREQ_VERY_HIGH
PD13.Signal=S_TIM4_CH2
PD14.GPIOParameters=GPIO_Speed,GPIO_Label
PD14.GPIO_Label=RADIO_C4
PD14.GPIO_Speed=GPIO_SPEED_FREQ_VERY_HIGH
PD14.Signal=S_TIM4_CH3
PD15.GPIOParameters=GPIO_Speed,GPIO_Label
PD15.GPIO_Label=RADIO_C3
PD15.GPIO_Speed=GPIO_SPEED_FREQ_VERY_HIGH
PD15.Signal=S_TIM4_CH4
PD2.Mode=SD_4_bits_Wide_bus
PD2.Signal=SDMMC1_CMD
PD3.GPIOParameters=GPIO_Label
PD3.GPIO_Label=DISP_D
PD3.Signal=GPIO_Output
PD4.GPIOParameters=GPIO_Label
PD4.GPIO_Label=DISP_C
PD4.Signal=GPIO_Output
PD5.GPIOParameters=GPIO_Label
PD5.GPIO_Label=DISP_B
PD5.Signal=GPIO_Output
PD6.GPIOParameters=GPIO_Label
PD6.GPIO_Label=DISP_A
PD6.Signal=GPIO_Output
PD7.GPIOParameters=GPIO_Label
PD7.GPIO_Label=DISP_DIG4
PD7.Signal=GPIO_Output
PD8.Mode=Asynchronous
PD8.Signal=USART3_TX
PD9.Mode=Asynchronous
PD9.Signal=USART3_RX
PE0.GPIOParameters=PinState,GPIO_PuPd,GPIO_Label
PE0.GPIO_Label=TPS55289_ENABLE
PE0.GPIO_PuPd=GPIO_NOPULL
PE0.PinState=GPIO_PIN_SET
PE0.Signal=GPIO_Output
PE1.GPIOParameters=PinState,GPIO_PuPd,GPIO_Label
PE1.GPIO_Label=MAX_RESET
PE1.GPIO_PuPd=GPIO_PULLUP
PE1.PinState=GPIO_PIN_SET
PE1.Signal=GPIO_Output
PE10.GPIOParameters=GPIO_Label
PE10.GPIO_Label=BUTTON_OK
PE10.Signal=GPIO_Input
PE11.GPIOParameters=GPIO_Label
PE11.GPIO_Label=BUTTON_F1
PE11.Signal=GPIO_Input
PE12.GPIOParameters=GPIO_Label
PE12.GPIO_Label=BUTTON_F2
PE12.Signal=GPIO_Input
PE13.GPIOParameters=GPIO_Label
PE13.GPIO_Label=BUTTON_F3
PE13.Signal=GPIO_Input
PE14.GPIOParameters=GPIO_Label
PE14.GPIO_Label=EXTRA_I2C_ENABLE
PE14.Signal=GPIO_Output
PE2.GPIOParameters=GPIO_Label
PE2.GPIO_Label=MAX_SCK
PE2.Mode=Full_Duplex_Master
PE2.Signal=SPI4_SCK
PE3.GPIOParameters=GPIO_PuPd,GPIO_Label
PE3.GPIO_Label=MAX_LOS
PE3.GPIO_PuPd=GPIO_NOPULL
PE3.Signal=GPIO_Input
PE4.GPIOParameters=GPIO_Label
PE4.GPIO_Label=MAX_CS
PE4.Mode=NSS_Signal_Hard_Output
PE4.Signal=SPI4_NSS
PE5.GPIOParameters=GPIO_Label
PE5.GPIO_Label=MAX_MISO
PE5.Mode=Full_Duplex_Master
PE5.Signal=SPI4_MISO
PE6.GPIOParameters=GPIO_Label
PE6.GPIO_Label=MAX_MOSI
PE6.Mode=Full_Duplex_Master
PE6.Signal=SPI4_MOSI
PE7.GPIOParameters=GPIO_Label
PE7.GPIO_Label=BUTTON_RIGHT
PE7.Signal=GPIO_Input
PE8.GPIOParameters=GPIO_Label
PE8.GPIO_Label=BUTTON_INCREASE
PE8.Signal=GPIO_Input
PE9.GPIOParameters=GPIO_Label
PE9.GPIO_Label=BUTTON_DECREASE
PE9.Signal=GPIO_Input
PH0/OSC_IN.Mode=HSE-External-Oscillator
PH0/OSC_IN.Signal=RCC_OSC_IN
PH1/OSC_OUT.Mode=HSE-External-Oscillator
PH1/OSC_OUT.Signal=RCC_OSC_OUT
RCC.HSE_VALUE=25000000
board=custom

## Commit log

2025-12-31 Updated project
    Flowchart and component definitions
2026-01-02 Added MCU Requirments
